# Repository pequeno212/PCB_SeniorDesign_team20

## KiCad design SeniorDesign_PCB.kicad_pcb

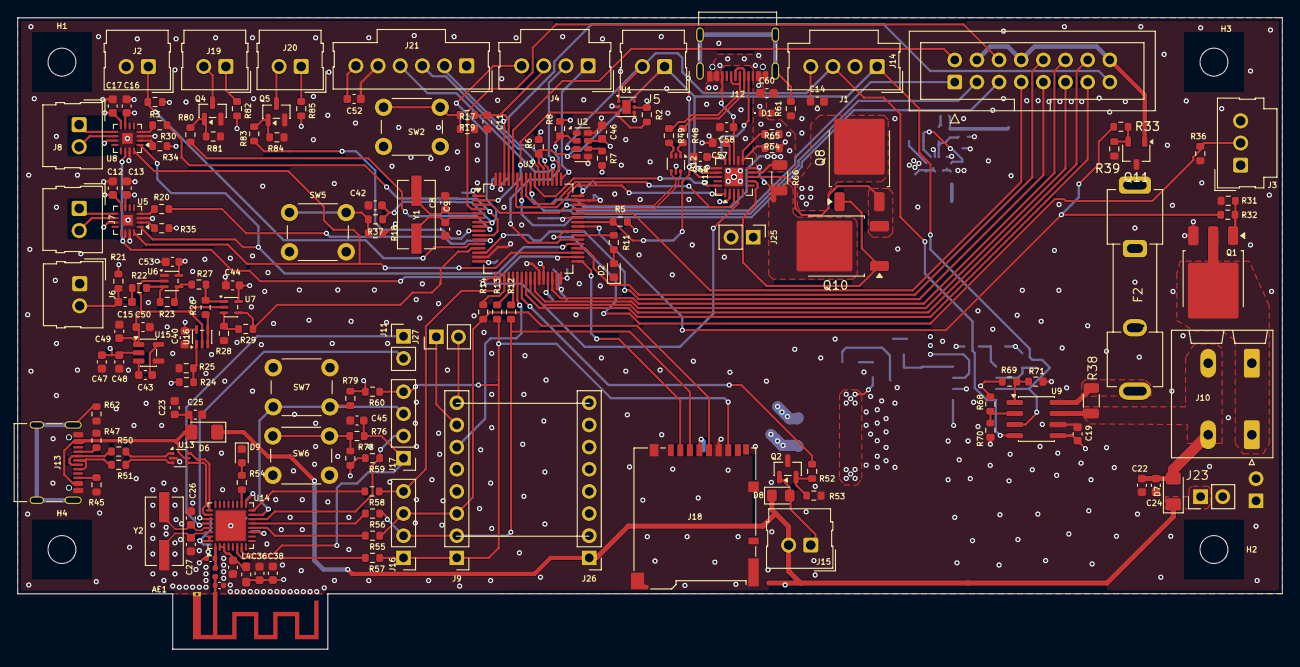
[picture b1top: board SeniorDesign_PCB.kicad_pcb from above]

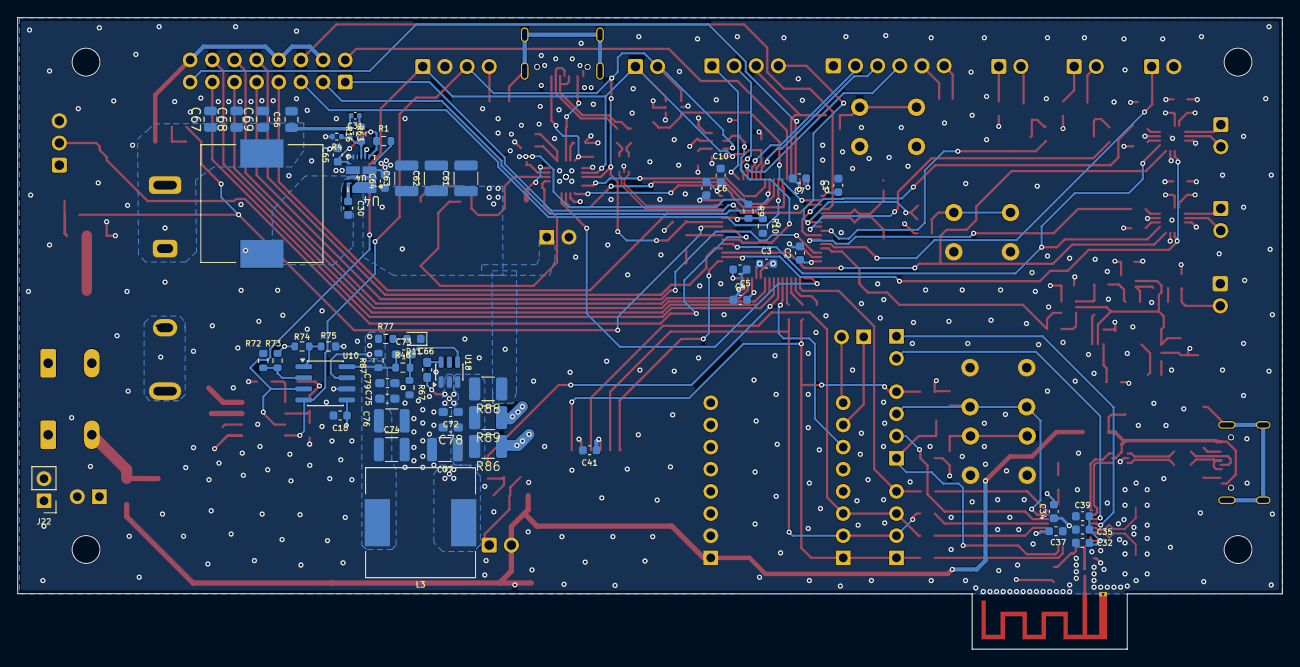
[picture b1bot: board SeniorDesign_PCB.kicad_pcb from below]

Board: 4 copper layers, 145.0 x 72.4 mm, 228 parts (59 on the bottom side), 155 nets.

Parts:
AE1: Antenna_Shield; Texas_SWRA117D_2.4GHz_Left
C1, C22, C23, C33, C39, C43, C48, C49, C65: 1u; C_0603_1608Metric
C2, C3, C4, C5, C6, C7, C10, C11, C13, C14, C17, C18, C19, C24, C25, C30, C32, C34, C35, C36, C37, C40, C41, C42, C44, C45, C46, C47, C50, C52, C53, C57, C64: 100n; C_0603_1608Metric
C8, C9, C26, C27: 22p; C_0603_1608Metric
C12, C16, C38: 10u; C_0603_1608Metric
C15: 1uF; C_0603_1608Metric
C28, C29: DNP; C_0402_1005Metric
C31: 470pF; C_0402_1005Metric
C56, C67, C68, C69: 22u; C_0805_2012Metric
C58, C59: 330p; C_0603_1608Metric
C60: 2u2; C_0603_1608Metric
C61, C62, C63: 22u; C_1210_3225Metric
C66, C72, C75: 100n; C_0603_1608Metric_Pad1.08x0.95mm_HandSolder
C73: 82p; C_0603_1608Metric_Pad1.08x0.95mm_HandSolder
C74: 47u; C_1210_3225Metric
C76: DNP; C_1210_3225Metric
C77: 15u; C_1210_3225Metric
C78, C79: DNP; C_0603_1608Metric_Pad1.08x0.95mm_HandSolder
D1: ESDA25P35-1U1M; ESDA25P351U1M
D2, D9, D11: LED; LED_0603_1608Metric
D6, D7: D; D_1206_3216Metric_Pad1.42x1.75mm_HandSolder
D8: D; D_0805_2012Metric_Pad1.15x1.40mm_HandSolder
F2: RGEF1400; Fuseholder_Clip-5x20mm_Keystone_3512P_Inline_P23.62x7.27mm_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
H1, H2, H3, H4: MountingHole; MountingHole_3.2mm_M3
J1, J4: Conn_01x04_Pin; Molex_SL_171971-0004_1x04_P2.54mm_Vertical
J2, J6, J7, J8, J19, J20: Conn_01x02_Socket; Molex_SL_171971-0002_1x02_P2.54mm_Vertical
J3: Conn_01x03_Socket; Molex_SL_171971-0003_1x03_P2.54mm_Vertical
J5, J15: Conn_01x02_Pin; Molex_SL_171971-0002_1x02_P2.54mm_Vertical
J9, J26: Conn_01x08_Socket; PinHeader_1x08_P2.54mm_Vertical
J10: Conn_01x02_Socket; PhoenixContact_SPT_2.5_2-H-5.0_1x02_P5.0mm_Horizontal
J11: Conn_01x02_Pin; PinHeader_1x02_P2.54mm_Vertical
J12, J13: USB_C_Receptacle_USB2.0_14P; USB_C_Receptacle_Palconn_UTC16-G
J14: IDC_Cable_02x08; IDC-Header_2x08_P2.54mm_Vertical
J16, J17: Conn_01x04_Pin; PinHeader_1x04_P2.54mm_Vertical
J18: Micro_SD_Card; microSD_HC_Hirose_DM3BT-DSF-PEJS
J21: MIC_I2S_CONNECTOR; Molex_SL_171971-0006_1x06_P2.54mm_Vertical
J22, J23, J25, J27: Conn_01x02_Socket; PinHeader_1x02_P2.54mm_Vertical
L2: DNP; L_0402_1005Metric
L3: 10u; L_12x12mm_H6mm
L4: 2n; L_0603_1608Metric_Pad1.05x0.95mm_HandSolder
L10: 1.5u; IHLP5050EZER1R5M01
Q1: NMOS; TO-252-3_TabPin2
Q2: NMOS; SOT-23
Q4, Q5: AO3400A; SOT-23
Q8, Q10: NMOS; TO-252-2
Q11: NMOS; TSOT-23
R1, R36, R46: 100k; R_0603_1608Metric
R2, R7, R8, R17, R18, R24, R25, R32, R39, R53, R59, R60, R64, R78, R79, R81, R84: 10k; R_0603_1608Metric
R3, R21: 2k2; R_0603_1608Metric
R4: 10k; R_0402_1005Metric
R5, R6, R45, R47: 5k1; R_0603_1608Metric
R9: 17k; R_0603_1608Metric
R10: 3.3k; R_0603_1608Metric
R11, R54, R77: 330; R_0603_1608Metric
R12, R13, R14, R20, R34, R35, R55, R56, R57, R58, R69, R70, R72, R75: 0R; R_0603_1608Metric
R16, R19, R22, R26, R27, R28, R29, R37, R76: 1k; R_0603_1608Metric
R23: 18k; R_0603_1608Metric
R30: 210k; R_0603_1608Metric
R31, R33, R52: 10R; R_0603_1608Metric
R38: 2m; R_1206_3216Metric
R48, R49, R50, R51: 22R; R_0603_1608Metric
R61, R62, R68, R71, R73, R74: DNP; R_0603_1608Metric
R63: 73.2k; R_0402_1005Metric
R65: 560; R_0603_1608Metric
R66: 10m; R_1206_3216Metric
R67: 22k; R_0603_1608Metric
R80, R83: 10; R_0603_1608Metric
R82, R85: 17; R_0603_1608Metric
R86, R89: DNP; R_1210_3225Metric_Pad1.30x2.65mm_HandSolder
R87: 2m; R_0603_1608Metric
R88: 0; R_1210_3225Metric_Pad1.30x2.65mm_HandSolder
SW2, SW5, SW6, SW7: SW_Push; SW_PUSH_6mm
U1: TMP117xxDRV; WSON-6-1EP_2x2mm_P0.65mm_EP1x1.6mm
U2: RV-3028-C7; MicroCrystal_C7_SON-8_1.5x3.2mm_P0.9mm
U3: STM32G474RETx; LQFP-64_10x10mm_P0.5mm
U4: TPS51388VABR; VAB0013A-MFG
U5, U8: MAX98357A; TQFN-16-1EP_3x3mm_P0.5mm_EP1.23x1.23mm
U6, U7, U16: TLV172IDCK; SOT-353_SC-70-5
U9, U10: INA219AxD; SOIC-8_3.9x4.9mm_P1.27mm
U12, U13: USBLC6-2P6; SOT-666
U14: ESP32-C3FH4; QFN-32-1EP_5x5mm_P0.5mm_EP3.45x3.45mm
U15: TPS60400DBV; SOT-23-5
U17: TCPP03-M20; TQFN-20-1EP_4x4mm_P0.5mm_EP2.1x2.1mm
U18: TPS54302; SOT-23-6
Y1: 16MHz; Crystal_SMD_ECS_CSM3X-2Pin_7.6x4.1mm
Y2: 40MHz; Crystal_SMD_ECS_CSM3X-2Pin_7.6x4.1mm

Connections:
3V3: C1.1, C2.1, C3.1, C4.1, C5.1, C6.1, C7.1, C10.1, C12.1, C13.1, C14.1, C16.1, C17.1, C18.1, C19.1, C32.1, C34.1, C35.1, C36.1, C37.1, C38.1, C39.1, C40.1, C41.1, C44.1, C46.1, C47.1, C48.1, C52.1, C53.1, J1.4, J3.1, J18.4 (VDD), J21.6, J22.1, J26.3, L4.2, R2.1, R3.1, R5.2, R6.2, R7.1, R8.1, R18.1, R21.1, R24.2, R34.1, R35.1, R59.1, R60.1, R68.2, R69.2, R72.2, R74.2, R77.1, R78.1, R79.1, R82.1, R85.1, R87.2, SW2.2, U1.5 (V+), U2.7 (VDD), U3.1 (VBAT), U3.16 (VDD), U3.28 (VREF+), U3.29 (VDDA), U3.32 (VDD), U3.48 (VDD), U3.64 (VDD), U4.6 (EN), U5.7 (VDD), U5.8 (VDD), U6.5 (V+), U7.5 (V+), U8.7 (VDD), U8.8 (VDD), U9.5 (VS), U10.5 (VS), U10.7 (IN-), U12.5 (VBUS), U14.11 (VDD3P3_RTC), U14.17 (VDD3P3_CPU), U14.31 (VDDA), U14.32 (VDDA), U15.2 (IN), U16.5 (V+), U17.2 (VCC_{VCONN})
5V: D6.1 (K), D7.1 (K), D8.1 (K), J15.2, J23.1, J26.1, R89.1
20V: C61.1, C62.1, C63.1, C64.1, J25.1, Q8.2 (D), R88.1, U4.1 (VIN)
-3V3: C49.1, C50.1, U6.2 (V-), U7.2 (V-), U15.1 (OUT), U16.2 (V-)
/Analog/I2S2_CK: U3.35 (PB13), U5.16 (BCLK), U8.16 (BCLK)
/Analog/I2S2_SD: U3.37 (PB15), U5.1 (DIN), U8.1 (DIN)
/Analog/I2S2_WS: U3.34 (PB12), U5.14 (LRCLK), U8.14 (LRCLK)
/Analog/LEFT_SD_MODE: R20.1, U3.11 (PC3)
/Analog/MIC: R29.1, U3.13 (PA1), U7.4
/Analog/RIGHT_SD_MODE: R30.1, U3.10 (PC2)
/ESP32C3/BOOT: J17.3, R79.2, SW7.1, U14.15 (GPIO9/BOOT)
/ESP32C3/ESP32_RST: C45.1, J17.1, R76.1, U14.7 (CHIP_EN)
/ESP32C3/ESP32_USB_D_N: U13.6 (I/O1), U14.25 (GPIO18/USB_D-)
/ESP32C3/ESP32_USB_D_P: U13.4 (I/O2), U14.26 (GPIO19/USB_D+)
/ESP32C3/GPIO8: J17.2, R59.2, U14.14 (GPIO8)
/ESP32C3/LNA_IN: C29.1, L2.2, U14.1 (LNA_IN)
/ESP32C3/RF_ANT: AE1.1 (A), C28.1, L2.1
/ESP32C3/SPI1_CS_ESP: J16.4, R58.2, U3.18 (PA4)
/ESP32C3/SPI1_MISO: J9.1, J16.1, J17.4, J18.7 (DAT0), R13.2, R57.2, R60.2
/ESP32C3/SPI1_MOSI: J9.2, J16.2, J18.3 (CMD), R12.2, R56.1
/ESP32C3/SPI1_SCLK: J9.3, J16.3, J18.5 (CLK), R14.2, R55.1
/ESP32C3/TEST_LED: R54.1, U14.18 (GPIO11)
/ESP32C3/UART_RX: J11.2, U14.27 (GPIO20)
/ESP32C3/UART_TX: J11.1, U14.28 (GPIO21)
/ESP32C3/XTAL_N: C26.1, U14.29 (XTAL_N), Y2.2
/ESP32C3/XTAL_P: C27.1, U14.30 (XTAL_P), Y2.1
/Peripherals/5V_Buck: C22.1, C24.1, D7.2 (A), J10.2, R38.2, U9.7 (IN-)
/Peripherals/FAN_PWM: R52.2, U3.23 (PC5)
/Peripherals/INT_RTC: R8.2, U2.2 (~INT), U3.38 (PC6)
/Peripherals/MATRIX_A: J14.9 (Pin_5), U3.14 (PA2)
/Peripherals/MATRIX_B: J14.10 (Pin_12), U3.36 (PB14)
/Peripherals/MATRIX_B1: J14.3 (Pin_2), U3.56 (PB3)
/Peripherals/MATRIX_B2: J14.7 (Pin_4), U3.44 (PA10)
/Peripherals/MATRIX_C: J14.11 (Pin_6), U3.26 (PB2)
/Peripherals/MATRIX_CLK: J14.13 (Pin_7), U3.24 (PB0)
/Peripherals/MATRIX_D: J14.12 (Pin_11), U3.30 (PB10)
/Peripherals/MATRIX_G1: J14.2 (Pin_16), U3.60 (PB7)
/Peripherals/MATRIX_G2: J14.6 (Pin_14), U3.4 (PC15)
/Peripherals/MATRIX_LAT: J14.14 (Pin_10), U3.25 (PB1)
/Peripherals/MATRIX_OE: J14.15 (Pin_8), U3.62 (PB9)
/Peripherals/MATRIX_PWR_EN: R31.1, R33.1, U3.41 (PC9)
/Peripherals/MATRIX_R1: J14.1, U3.3 (PC14)
/Peripherals/MATRIX_R2: J14.5 (Pin_3), U3.58 (PB5)
/Peripherals/SPI_CS_ESPMini: J9.6, U3.22 (PC4)
/Peripherals/SPI_CS_SD_CARD: J18.2 (DAT3/CD), U3.33 (PB11)
/Peripherals/UART_RX_Mini: J9.8, J27.2
/Peripherals/UART_TX_Mini: J9.7, J27.1
/Peripherals/USB_N_ESP_ESD: R50.2, U13.1 (I/O1)
/Peripherals/USB_N_ESP_RES: J13.A7 (D-), J13.B7 (D-), R50.1
/Peripherals/USB_P_ESP_ESD: R51.2, U13.3 (I/O2)
/Peripherals/USB_P_ESP_RES: J13.A6 (D+), J13.B6 (D+), R51.1
/Peripherals/VBUS_ESP: C23.1, C25.1, D6.2 (A), J13.A4 (VBUS), J13.A9 (VBUS), J13.B4 (VBUS), J13.B9 (VBUS), U13.5 (VBUS)
/Power/3V3_AMPS_1: C73.1, C74.1, C75.1, C76.1, C79.1, L3.2, R46.1, R87.1, U10.8 (IN+)
/Power/5V_AMPS_1: F2.2, R38.1, U9.8 (IN+)
/Power/I2C3_SCL: J1.3, J5.2, R5.1, U1.1 (SCL), U2.3 (SCL), U3.42 (PA8), U9.4 (SCL), U10.4 (SCL), U17.18 (SCL)
/Power/I2C3_SDA: J1.1, J5.1, R6.1, U1.6 (SDA), U2.4 (SDA), U3.53 (PC11), U9.3 (SDA), U10.3 (SDA), U17.17 (SDA)
/Power/I_ANA: U3.17 (PA3), U17.4 (I_{ANA})
/Power/PD_EN: U3.55 (PD2), U17.20 (EN)
/Power/STM32_USB_D_N: U3.45 (PA11), U12.6 (I/O1)
/Power/STM32_USB_D_P: U3.46 (PA12), U12.4 (I/O2)
/Power/USBPD_CC1: U3.59 (PB6), U17.1 (CC1)
/Power/USBPD_CC2: U3.57 (PB4), U17.3 (CC2)
/Power/USB_N_STM_ESD: R48.2, U12.1 (I/O1)
/Power/USB_N_STM_RES: J12.A7 (D-), J12.B7 (D-), R48.1
/Power/USB_P_STM_ESD: R49.2, U12.3 (I/O2)
/Power/USB_P_STM_RES: J12.A6 (D+), J12.B6 (D+), R49.1
/Power/VBUS_STM: C60.1, D1.1 (K), J12.A4 (VBUS), J12.A9 (VBUS), J12.B4 (VBUS), J12.B9 (VBUS), R9.1, R64.1, R66.1, R86.1, U17.9 (VBUS_{c})
/STM32G4/ALS_ADC: J2.1, R3.2, U3.12 (PA0)
/STM32G4/BOOT0: C11.1, J4.3, R19.1, U3.61 (PB8)
/STM32G4/CLK_IN: C8.1, U3.5 (PF0), Y1.2
/STM32G4/CLK_OUT: C9.1, U3.6 (PF1), Y1.1
/STM32G4/I2S3_CK: J21.2, U3.52 (PC10)
/STM32G4/I2S3_SD: J21.3, U3.54 (PC12)
/STM32G4/I2S3_WS: J21.4, U3.51 (PA15)
/STM32G4/INT_TEMP_ALERT: R2.2, U1.3 (ALERT), U3.2 (PC13)
/STM32G4/PAPIR: J3.2, R36.1, U3.40 (PC8)
/STM32G4/SPI1_MISO0: R13.1, U3.20 (PA6)
/STM32G4/SPI1_MOSI0: R12.1, U3.21 (PA7)
/STM32G4/SPI1_SCLK0: R14.1, U3.19 (PA5)
/STM32G4/SWDCLK: J4.2, U3.50 (PA14)
/STM32G4/SWDIO: J4.1, U3.49 (PA13)
/STM32G4/TEST_LED: R11.1, U3.39 (PC7)
/STM32G4/TV_IR_PWM_1: R80.2, U3.8 (PC0)
/STM32G4/TV_IR_PWM_2: R83.2, U3.9 (PC1)
/STM32G4/USB_VBUS_DETECT: R9.2, R10.1, U3.43 (PA9)
/STM32G4/nRST: C42.1, J4.4, R37.1, U3.7 (PG10)
GND: AE1.2 (Shield), C1.2, C2.2, C3.2, C4.2, C5.2, C6.2, C7.2, C8.2, C9.2, C10.2, C11.2, C12.2, C13.2, C14.2, C16.2, C17.2, C18.2, C19.2, C22.2, C23.2, C24.2, C25.2, C26.2, C27.2, C28.2, C29.2, C32.2, C33.2, C34.2, C35.2, C36.2, C37.2, C38.2, C39.2, C40.2, C41.2, C42.2, C44.2, C45.2, C46.2, C47.2, C48.2, C49.2, C50.2, C52.2, C53.2, C56.2, C57.2, C58.2, C59.2, C60.2, C61.2, C62.2, C63.2, C64.2, C65.2, C67.2, C68.2, C69.2, C72.2, C74.2, C75.2, C76.2, C77.2, C78.2, C79.2, D1.2 (A), D2.1 (K), D9.1 (K), D11.1 (K), J1.2, J2.2, J3.3, J6.1, J12.A1 (GND), J12.A12 (GND), J12.B1 (GND), J12.B12 (GND), J13.A1 (GND), J13.A12 (GND), J13.B1 (GND), J13.B12 (GND), J18.6 (VSS), J18.SH (SHIELD), J21.1, J21.5, J22.2, J23.2, J25.2, J26.2, Q1.3 (S), Q2.3 (S), Q4.2 (S), Q5.2 (S), Q11.3 (S), R4.2, R10.2, R17.2, R25.1, R28.1, R32.2, R36.2, R39.2, R45.1, R47.1, R53.1, R61.1, R62.1, R65.2, R67.2, R70.1, R71.1, R73.1, R75.1, R81.2, R84.2, SW5.2, SW6.2, SW7.2, U1.2 (GND), U1.4 (ADD0), U2.5 (VSS), U2.8 (EVI), U3.15 (VSS), U3.27 (VSSA), U3.31 (VSS), U3.47 (VSS), U3.63 (VSS), U4.3 (PGND), U4.9 (FBG), U4.11 (PGND), U5.3 (GND), U5.11 (GND), U5.15 (GND), U5.17 (PAD), U6.1 (+), U8.3 (GND), U8.11 (GND), U8.15 (GND), U8.17 (PAD), U9.6 (GND), U10.6 (GND), U12.2 (GND), U13.2 (GND), U14.33 (GND), U15.4 (GND), U17.12 (GND), U17.16 (I2C_{ADD}), U17.21 (GND), U18.1 (GND)
unnamed: C15.1, R22.1
unnamed: C30.2, L10.1, U4.2 (SW), U4.12 (SW)
unnamed: C31.1, R16.2
unnamed: C31.2, C56.1, C67.1, C68.1, C69.1, F2.1, L10.2, R63.1
unnamed: D2.2 (A), R11.2
unnamed: D8.2 (A), J15.1, Q2.1 (D)
unnamed: D9.2 (A), R54.2
unnamed: D11.2 (A), R77.2
unnamed: C15.2, J6.2, R21.2
unnamed: J7.1, U5.9 (OUTP)
unnamed: J7.2, U5.10 (OUTN)
unnamed: J8.1, U8.9 (OUTP)
unnamed: J8.2, U8.10 (OUTN)
unnamed: J10.1, Q1.2 (D)
unnamed: C59.1, J12.A5 (CC1), U17.15 (CC1_{c})
unnamed: C58.1, J12.B5 (CC2), U17.13 (CC2_{c})
unnamed: J12.SH (SHIELD), R61.2
unnamed: J13.A5 (CC1), R47.2
unnamed: J13.B5 (CC2), R45.2
unnamed: J13.SH (SHIELD), R62.2
unnamed: J14.4 (Pin_15), J14.8 (Pin_13), J14.16 (Pin_9), Q11.1 (D)
unnamed: J19.1, R82.2
unnamed: J19.2, Q4.3 (D)
unnamed: J20.1, R85.2
unnamed: J20.2, Q5.3 (D)
unnamed: Q1.1 (G), R31.2, R32.1
unnamed: Q2.2 (G), R52.1, R53.2
unnamed: Q4.1 (G), R80.1, R81.1
unnamed: Q5.1 (G), R83.1, R84.1
unnamed: Q10.2 (D), R66.2, U17.10 (I_{sense})
unnamed: Q8.1 (G), Q10.1 (G), U17.7 (GDC_{g})
unnamed: Q8.3 (S), Q10.3 (S), U17.8 (GDC_{s})
unnamed: Q11.2 (G), R33.2, R39.1
unnamed: R17.1, R19.2, SW2.1
unnamed: R18.2, R37.2, SW5.1
unnamed: R23.2, R27.1, U6.4
unnamed: R76.2, R78.2, SW6.1
unnamed: R7.2, U2.6 (VBACKUP)
unnamed: R4.1, R16.1, R63.2, U4.7 (FB)
unnamed: C65.1, R1.1, U4.5 (MODE), U4.10 (VCC)
unnamed: R1.2, U4.4 (PG)
unnamed: C30.1, U4.13 (VBST)
unnamed: R35.2, U5.2 (GAIN_SLOT)
unnamed: R20.2, U5.4 (~SD_MODE)
unnamed: R22.2, R23.1, U6.3 (-)
unnamed: R26.2, R27.2, U7.1 (+)
unnamed: R28.2, R29.2, U7.3 (-)
unnamed: R34.2, U8.2 (GAIN_SLOT)
unnamed: R30.2, U8.4 (~SD_MODE)
unnamed: R68.1, R70.2, U9.2 (A0)
unnamed: R69.1, R71.2, U9.1 (A1)
unnamed: R72.1, R73.2, U10.2 (A0)
unnamed: R74.1, R75.2, U10.1 (A1)
unnamed: R57.1, U14.6 (GPIO2)
unnamed: R55.2, U14.12 (GPIO6)
unnamed: R56.2, U14.13 (GPIO7)
unnamed: R58.1, U14.16 (GPIO10)
unnamed: C43.1, U15.5 (C_{FLY+})
unnamed: C43.2, U15.3 (C_{FLY-})
unnamed: R24.1, R25.2, U16.1 (+)
unnamed: R26.1, U16.3 (-), U16.4
unnamed: C57.1, U17.14 (C_{BIAS})
unnamed: R64.2, R65.1, U17.11 (V_{sense})
unnamed: C66.1, U18.6 (BOOT)
unnamed: C73.2, R46.2, R67.1, U18.4 (FB)
unnamed: C66.2, L3.1, U18.2 (SW)
unnamed: C72.1, C77.1, C78.1, R86.2, R88.2, R89.2, U18.3 (VIN)
VDD3P3: C33.1, L4.1, U14.2 (VDD3P3), U14.3 (VDD3P3)
